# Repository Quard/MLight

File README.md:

# MLight

MLight is a compact, all-in-one control board designed to manage auxiliary tools for soldering equipment. It was primarily developed for an affordable Chinese digital microscope, aiming to reduce the number of power cords and to integrate lighting for the microscope. Additionally, it can control the fan of a basic DIY fume extractor, built using a PC fan and an aquarium coal filter, and provide power to a small external HDMI display for the microscope.

Features of the Control Board:

* Capable of being powered by an external DC 12V source or a QuickChange USB source.
* Bypasses power to the microscope only when the voltage is at 12V.
* Custom ring light with PWM (Pulse Width Modulation) brightness control.
* The PWM for the light is configurable at frequencies of 1 kHz, 4 kHz, 8 kHz, or 16 kHz to prevent image distortion from the microscope.
* Provides a 12V output for PC fan with PWM speed control support for the DIY fume extractor.
* Features a USB output of 1.5A for powering an external HDMI display.
* Includes an OLED display and encoder for easy control.
* Equipped with external EEPROM memory for storing and restoring settings.

[A brief demonstration video of the system in operation.](https://youtube.com/shorts/ih5DoEOJhLI)

## Controls

| Action | Description |
|--------|-------------|
| Encoder short press | Switch between fan and light |
| Encoder rotate | Change the value of current selected element |
| Encoder long press | Disable/enable fan and light |
| Encoder rotate pressed | Change the light PWM frequency |

## Project parts

### Firmware

The `firmware` folder includes an STM32CubeIDE CMake project, with all source code developed using CMSIS.

### Control Board

The KiCad project is located in the `hardware/control_board` directory. It includes a BOM file in the project root and an interactive BOM (iBOM) in the `bom` folder to facilitate assembly.

### Ring Light

The same structure applies to the Ring Light project, with its root located in the `hardware/ring_light` directory. It also contains a BOM file in the project root and an interactive BOM (iBOM) in the `bom` folder to assist with assembly.

### 3d

The `3d` folder contains STL files and Fusion 360 source files for the brackets used to mount the control board and ring light onto a microscope stand.

## Display elements

## Components block diagram

## BOM

### Control Board

|Reference|Value|Qty|Manufacturer Part Number|LCSC|MOUSER|
|---------|-----|---|------------------------|----|------|
|C1,C4,C10|100nF|3|CL10B104KB8NNNC|C1591|187-CL10B104KB8NNNC |
|C2|4.7uF|1|CL21A475KAQNNNE|C1779|187-CL21A475KAQNNNE |
|C3,C7,C8|10uF|3|CL21A106KOQNNNE|C1713|187-CL21A106KOQNNNE |
|C5,C6,C9|10nF|3|CL10B103JB8NNNC|C7248|187-CL10B103JB8NNNC |
|C11,C12|22uF|2|CL31A226KAHNNNE|C12891|187-CL31A226KAHNNNE |
|D1,D2|B340|2|B340A-13-F|C85098|621-B340A-F|
|D3|LED|1|150060BS75000|C84266|710-150060BS75000|
|D4|LED|1|150060RS75000|C84263|710-150060RS75000|
|IC1|FZT1049ATA|1|FZT1049ATA|C73835|522-FZT1049ATA|
|J1|USB_A_Stacked|1| 67298-4090|C908455|538-67298-4090|
|J3|Light|1||C158012||
|J4|Fan|1|47053-3000|C19795120|538-47053-3000|
|J5|OLED SSD1306|1||||
|J7|USB_C_Receptacle_USB2.0|1|GSB1C211110DS1HR|C709357|523-GSB1C211110DS1HR|
|J8|Barrel_Jack|1|KLDHCX-0202-BP-LT|C720558|806-KLDHCX0202BPLT|
|J9|Conn_01x02|1||C158012||
|L1|4.7uH|1|IHLP2525CZER4R7M01|C553961|70-IHLP2525CZER4R7M1|
|Q1|AO3400A|1|AO3400A|C20917|942-IRLML6344TRPBF|
|R1,R2,R3,R4,R5,R6,R8,R10,R15|10k|9|RC0603FR-0710KL|C98220|603-RC0603FR-0710KL|
|R7|180k|1|RC0603FR-07180KL|C123419|603-RC0603FR-07180KL|
|R9,R11|2.2k|2|RC0603FR-072K2L|C114662|603-RC0603FR-072K2L|
|R12|33k|1|RC0603FR-0733KL|C126359|603-RC0603FR-0733KL|
|R13,R16|1k|2|RC0603FR-071KL|C22548|603-RC0603FR-071KL|
|R14|1.8k|1|RC0603FR-071K8L|C185354|603-RC0603FR-071K8L|
|SW4|RotaryEncoder_Switch|1|C18164805|652-PEC12R-4220F-S24|PEC12R-4220F-S0024|
|U1|STM32G030F6Px|1|STM32G030F6P6TR|C529330|511-STM32G030F6P6TR|
|U2|AP63205WU|1|AP63205WU-7|C2071056|621-AP63205WU-7|
|U3|M24C02-WMN|1|M24C02-RMN6TP|C83836|511-M24C02-RMN6TP|
|U4|NCP1117-3.3_SOT223|1|NCP1117ST33T3G|C26537|863-NCP1117ST33T3G|

### Ring Light

|Reference|Value|Qty|Manufacturer Part Number|LCSC|MOUSER|
|---------|-----|---|------------------------|----|------|
|D1,D2,D3,D4,D5,D6,D7,D8,D9,D10,D11,D12,D13,D14,D15,D16|LED|16|JE2835AWT-R-H40EA0000-N0000001|C5220767|941-JE2835AWTH40EAN|
|R1,R2,R3,R4|0|4|RC0603JR-070RL|C95177|603-RC0603JR-070RL|

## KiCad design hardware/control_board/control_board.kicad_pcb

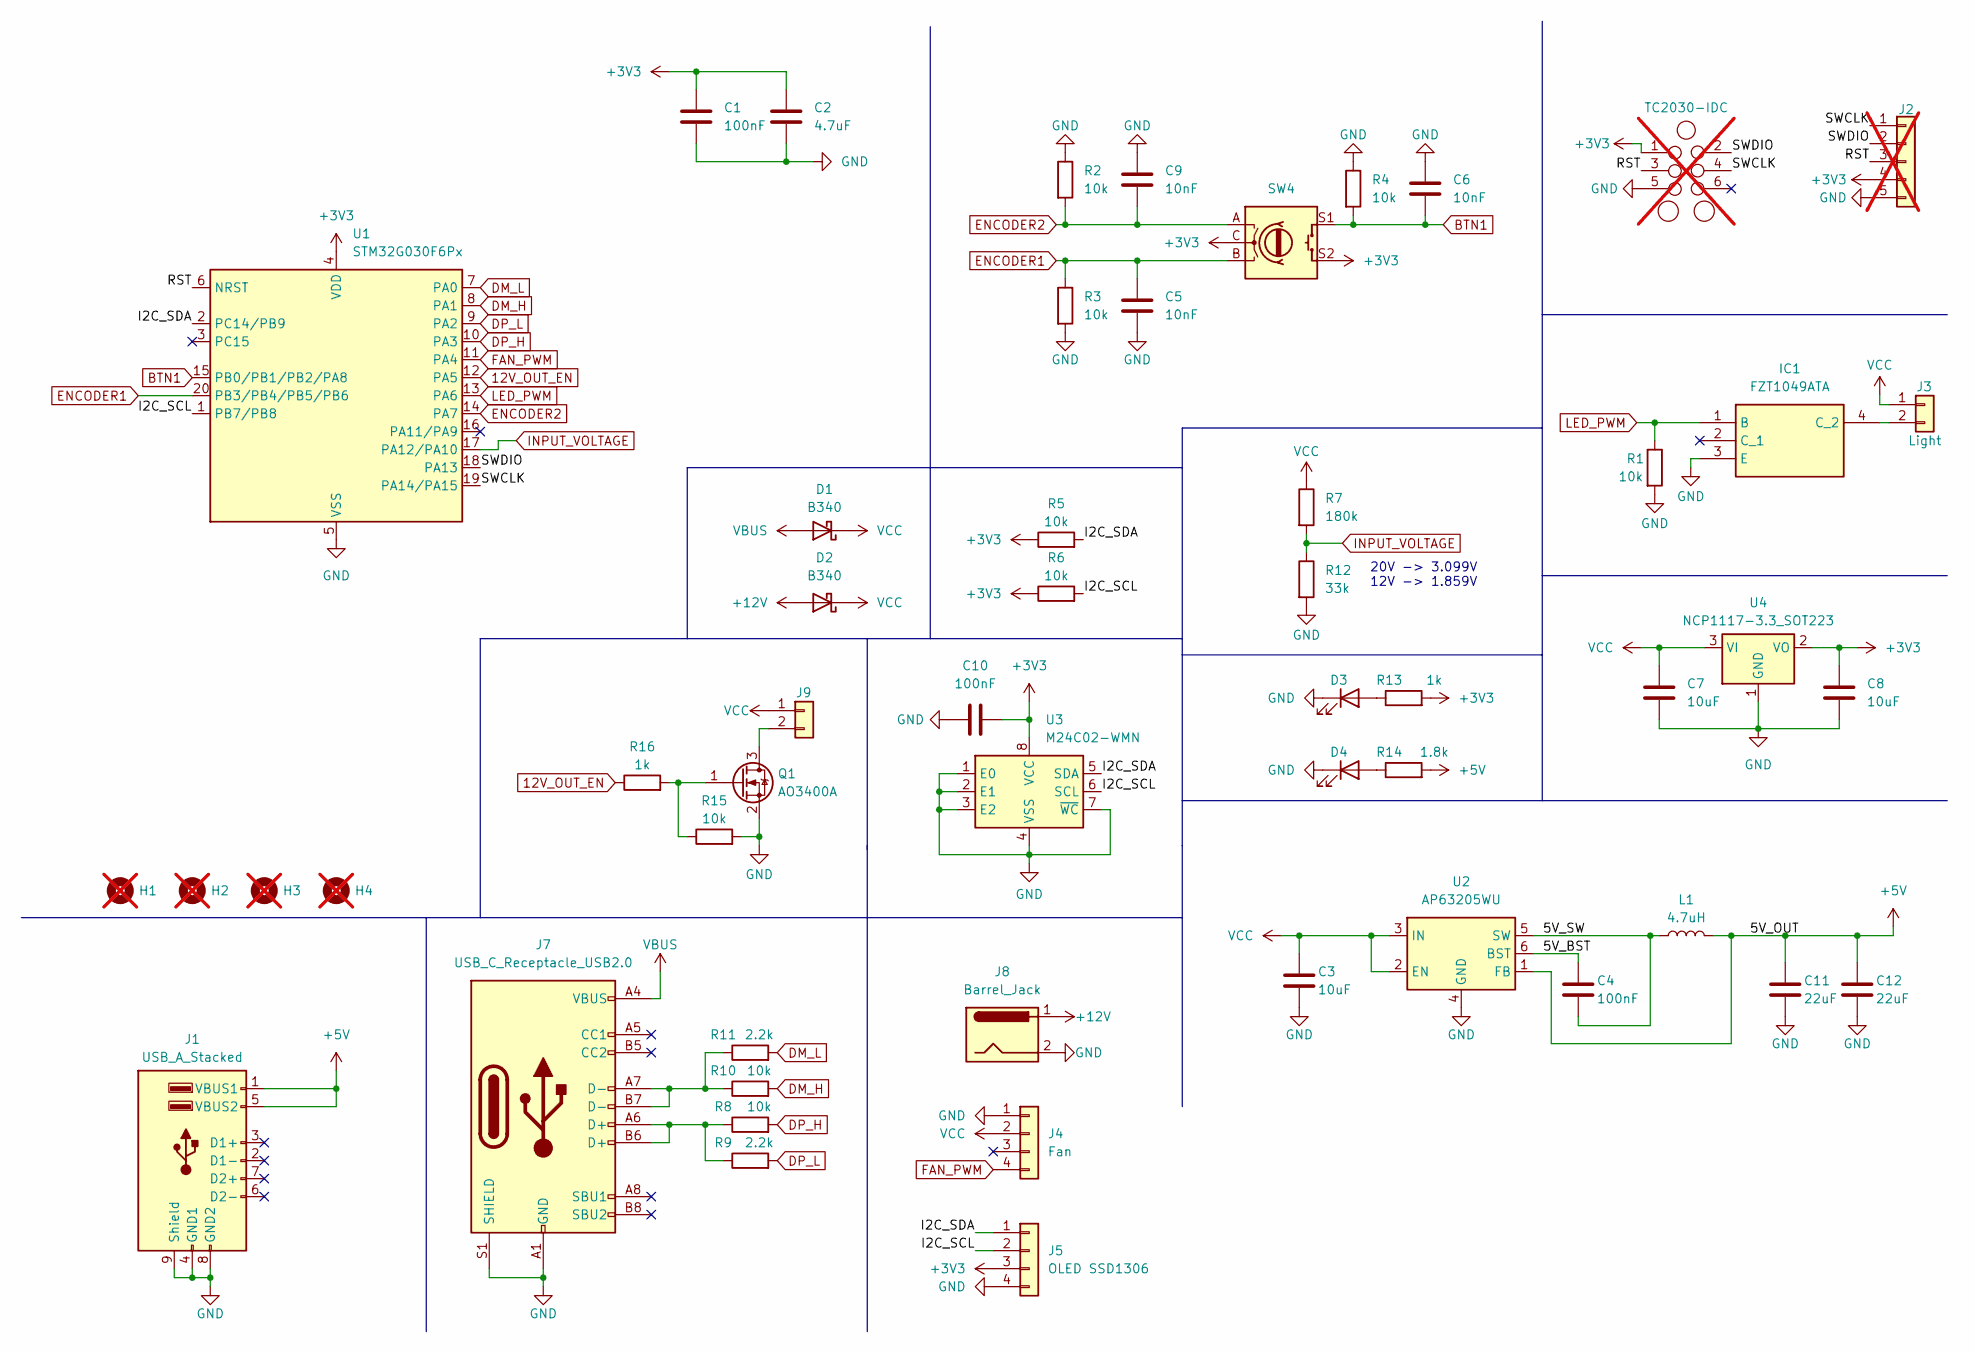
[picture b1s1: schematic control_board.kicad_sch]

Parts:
C1, C4, C10: 100nF; C_0603_1608Metric; Manufacturer_Part_Number CL10B104KB8NNNC; LCSC C1591
C2: 4.7uF; C_0805_2012Metric; Manufacturer_Part_Number CL21A475KAQNNNE; LCSC C1779
C3, C7, C8: 10uF; C_0805_2012Metric; Manufacturer_Part_Number CL21A106KOQNNNE; LCSC C1713
C5, C6, C9: 10nF; C_0603_1608Metric; Manufacturer_Part_Number CL10B103JB8NNNC; LCSC C7248
C11, C12: 22uF; C_1206_3216Metric; Manufacturer_Part_Number CL31A226KAHNNNE; LCSC C12891
D1, D2: B340; D_SMA; Manufacturer_Part_Number B340A-13-F; LCSC C85098
D3: LED; LED_0603_1608Metric; Manufacturer_Part_Number 150060BS75000; LCSC C84266
D4: LED; LED_0603_1608Metric; Manufacturer_Part_Number 150060RS75000; LCSC C84263
H1, H2, H3, H4: MountingHole; MountingHole_3.2mm_M3; not fitted
IC1: FZT1049ATA; SOT230P700X180-4N; Manufacturer_Part_Number FZT1049ATA; Mouser Part Number 522-FZT1049ATA
J1: USB_A_Stacked; USB_A_CUI_UJ2-ADH-TH_Horizontal_Stacked; Manufacturer_Part_Number 67298-4090; LCSC C908455
J2: Conn_01x05; PinHeader_1x05_P2.54mm_Vertical; not fitted
J3: Light; JST_XH_B2B-XH-A_1x02_P2.50mm_Vertical; LCSC C158012
J4: Fan; JST_XH_B4B-XH-A_1x04_P2.50mm_Vertical; Manufacturer_Part_Number 47053-3000; LCSC C19795120
J5: OLED SSD1306; JST_XH_B4B-XH-A_1x04_P2.50mm_Vertical
J6: TC2030-IDC; Tag-Connect_TC2030-IDC-NL_2x03_P1.27mm_Vertical; not fitted
J7: USB_C_Receptacle_USB2.0; USB_C_Receptacle_Palconn_UTC16-G; Manufacturer_Part_Number GSB1C211110DS1HR; LCSC C709357
J8: Barrel_Jack; BarrelJack_GCT_DCJ200-10-A_Horizontal; Manufacturer_Part_Number KLDHCX-0202-BP-LT; LCSC C720558
J9: Conn_01x02; JST_XH_B2B-XH-A_1x02_P2.50mm_Vertical; LCSC C158012
L1: 4.7uH; L_Vishay_IHLP-2525; Manufacturer_Part_Number IHLP2525CZER4R7M01; LCSC C553961
Q1: AO3400A; SOT-23; Manufacturer_Part_Number AO3400A; LCSC C20917
R1, R2, R3, R4, R5, R6, R8, R10, R15: 10k; R_0603_1608Metric; Manufacturer_Part_Number RC0603FR-0710KL; LCSC C98220
R7: 180k; R_0603_1608Metric; Manufacturer_Part_Number RC0603FR-07180KL; LCSC C123419
R9, R11: 2.2k; R_0603_1608Metric; Manufacturer_Part_Number RC0603FR-072K2L; LCSC C114662
R12: 33k; R_0603_1608Metric; Manufacturer_Part_Number RC0603FR-0733KL; LCSC C126359
R13, R16: 1k; R_0603_1608Metric; Manufacturer_Part_Number RC0603FR-071KL; LCSC C22548
R14: 1.8k; R_0603_1608Metric; Manufacturer_Part_Number RC0603FR-071K8L; LCSC C185354
SW4: RotaryEncoder_Switch; RotaryEncoder_Bourns_Vertical_PEC12R-3x17F-Sxxxx; Manufacturer_Part_Number 652-PEC12R-4220F-S24; LCSC C18164805
U1: STM32G030F6Px; TSSOP-20_4.4x6.5mm_P0.65mm; Manufacturer_Part_Number STM32G030F6P6TR; LCSC C529330
U2: AP63205WU; TSOT-23-6; Manufacturer_Part_Number AP63205WU-7; LCSC C2071056
U3: M24C02-WMN; SOIC-8_3.9x4.9mm_P1.27mm; Manufacturer_Part_Number M24C02-RMN6TP; LCSC C83836
U4: NCP1117-3.3_SOT223; SOT-223-3_TabPin2; Manufacturer_Part_Number NCP1117ST33T3G; LCSC C26537

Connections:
12V_OUT_EN: R16.1, U1.12 (PA5)
+3V3: C1.1, C2.1, C8.1, C10.2, J2.4, J5.3, J6.1, R5.1, R6.1, R13.2, SW4.C, SW4.S2, U1.4 (VDD), U3.8 (VCC), U4.2 (VO)
+5V: C11.1, C12.1, J1.1 (VBUS1), J1.5 (VBUS2), L1.2, R14.2, U2.1 (FB)
+12V: D2.2 (A), J8.1
/5V_BST: C4.1, U2.6 (BST)
/5V_SW: C4.2, L1.1, U2.5 (SW)
/I2C_SCL: J5.2, R6.2, U1.1 (PB7/PB8), U3.6 (SCL)
/I2C_SDA: J5.1, R5.2, U1.2 (PC14/PB9), U3.5 (SDA)
/RST: J2.3, J6.3, U1.6 (NRST)
/SWCLK: J2.1, J6.4, U1.19 (PA14/PA15)
/SWDIO: J2.2, J6.2, U1.18 (PA13)
BTN1: C6.2, R4.2, SW4.S1, U1.15 (PB0/PB1/PB2/PA8)
DM_H: R10.2, U1.8 (PA1)
DM_L: R11.2, U1.7 (PA0)
DP_H: R8.2, U1.10 (PA3)
DP_L: R9.2, U1.9 (PA2)
ENCODER1: C5.1, R3.1, SW4.B, U1.20 (PB3/PB4/PB5/PB6)
ENCODER2: C9.2, R2.2, SW4.A, U1.14 (PA7)
FAN_PWM: J4.4, U1.11 (PA4)
GND: C1.2, C2.2, C3.2, C5.2, C6.1, C7.2, C8.2, C9.1, C10.1, C11.2, C12.2, D3.1 (K), D4.1 (K), IC1.3 (E), J1.4 (GND1), J1.8 (GND2), J1.9 (Shield), J2.5, J4.1, J5.4, J6.5, J7.A1 (GND), J7.A12 (GND), J7.B1 (GND), J7.B12 (GND), J7.S1 (SHIELD), J8.2, Q1.2 (S), R1.2, R2.1, R3.2, R4.1, R12.2, R15.2, U1.5 (VSS), U2.4 (GND), U3.1 (E0), U3.2 (E1), U3.3 (E2), U3.4 (VSS), U3.7 (~WC), U4.1 (GND)
INPUT_VOLTAGE: R7.2, R12.1, U1.17 (PA12/PA10)
LED_PWM: IC1.1 (B), R1.1, U1.13 (PA6)
unnamed: D3.2 (A), R13.1
unnamed: D4.2 (A), R14.1
unnamed: IC1.4 (C_2), J3.2
unnamed: J7.A6 (D+), J7.B6 (D+), R8.1, R9.1
unnamed: J7.A7 (D-), J7.B7 (D-), R10.1, R11.1
unnamed: J9.2, Q1.3 (D)
unnamed: Q1.1 (G), R15.1, R16.2
VBUS: D1.2 (A), J7.A4 (VBUS), J7.A9 (VBUS), J7.B4 (VBUS), J7.B9 (VBUS)
VCC: C3.1, C7.1, D1.1 (K), D2.1 (K), J3.1, J4.2, J9.1, R7.1, U2.2 (EN), U2.3 (IN), U4.3 (VI)

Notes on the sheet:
20V -> 3.099V 12V -> 1.859V

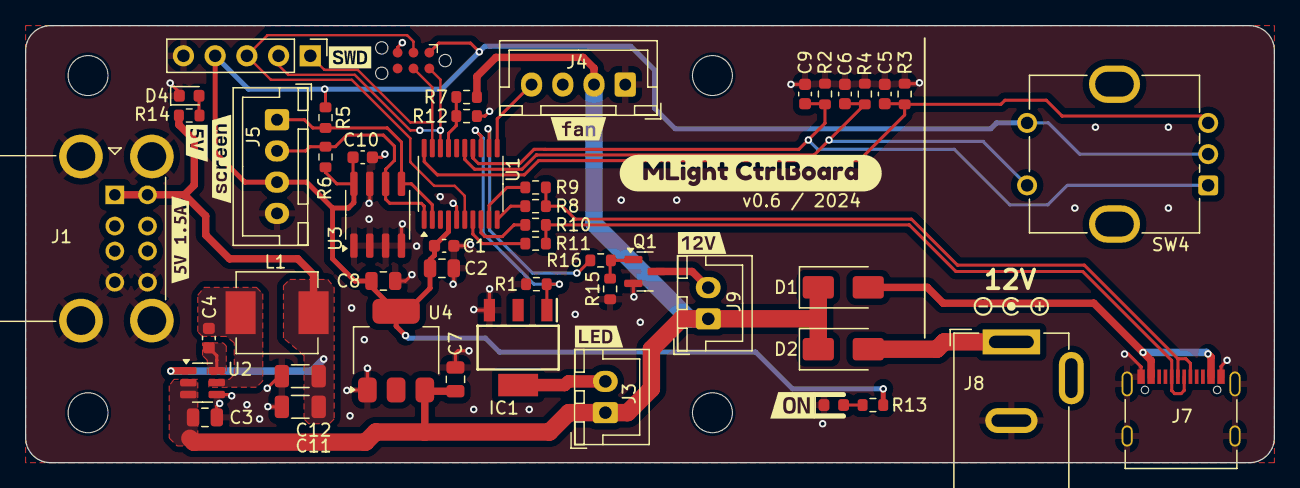
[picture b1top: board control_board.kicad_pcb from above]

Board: 2 copper layers, 100.0 x 35.0 mm, 62 parts (0 on the bottom side), 31 nets.

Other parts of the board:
kibuzzard-64DFCA22: G***; kibuzzard-64DFCA22
kibuzzard-64E1B8AF: G***; kibuzzard-64E1B8AF
kibuzzard-64E1B90C: G***; kibuzzard-64E1B90C
kibuzzard-64E666E4: G***; kibuzzard-64E666E4
kibuzzard-65854A39: G***; kibuzzard-65854A39
kibuzzard-6585330A: G***; kibuzzard-6585330A
kibuzzard-6585337F: G***; kibuzzard-6585337F
kibuzzard-65853391: G***; kibuzzard-65853391
kibuzzard-65855076: G***; kibuzzard-65855076

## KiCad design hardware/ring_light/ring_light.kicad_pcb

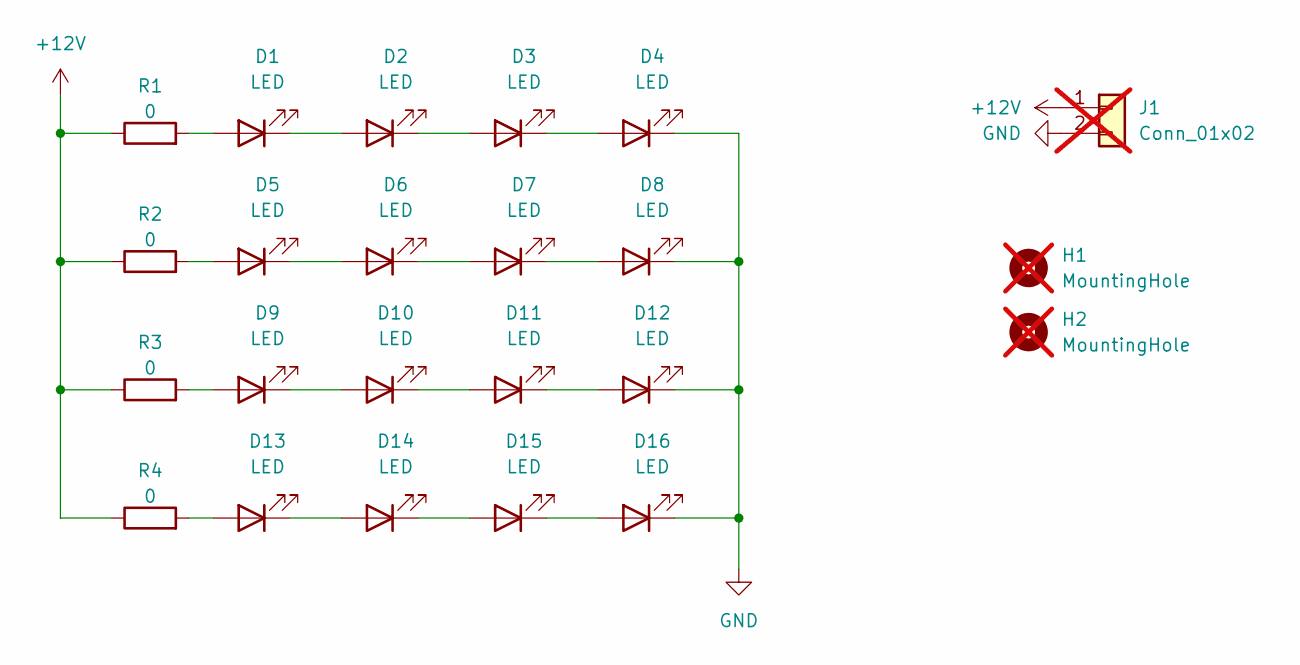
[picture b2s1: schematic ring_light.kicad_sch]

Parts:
D1, D2, D3, D4, D5, D6, D7, D8, D9, D10, D11, D12, D13, D14, D15, D16: LED; LED_PLCC_2835; Manufacturer Part Number JE2835AWT-R-H40EA0000-N0000001; LCSC C5220767
H1, H2: MountingHole; MountingHole_3.2mm_M3; not fitted
J1: Conn_01x02; PinHeader_1x02_P2.54mm_Vertical; not fitted
R1, R2, R3, R4: 0; R_0603_1608Metric; Manufacturer Part Number RC0603JR-070RL; LCSC C95177

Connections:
+12V: J1.1, R1.1, R2.1, R3.1, R4.1
GND: D4.1 (K), D8.1 (K), D12.1 (K), D16.1 (K), J1.2
unnamed: D1.2 (A), R1.2
unnamed: D1.1 (K), D2.2 (A)
unnamed: D2.1 (K), D3.2 (A)
unnamed: D3.1 (K), D4.2 (A)
unnamed: D5.2 (A), R2.2
unnamed: D5.1 (K), D6.2 (A)
unnamed: D6.1 (K), D7.2 (A)
unnamed: D7.1 (K), D8.2 (A)
unnamed: D9.2 (A), R3.2
unnamed: D9.1 (K), D10.2 (A)
unnamed: D10.1 (K), D11.2 (A)
unnamed: D11.1 (K), D12.2 (A)
unnamed: D13.2 (A), R4.2
unnamed: D13.1 (K), D14.2 (A)
unnamed: D14.1 (K), D15.2 (A)
unnamed: D15.1 (K), D16.2 (A)

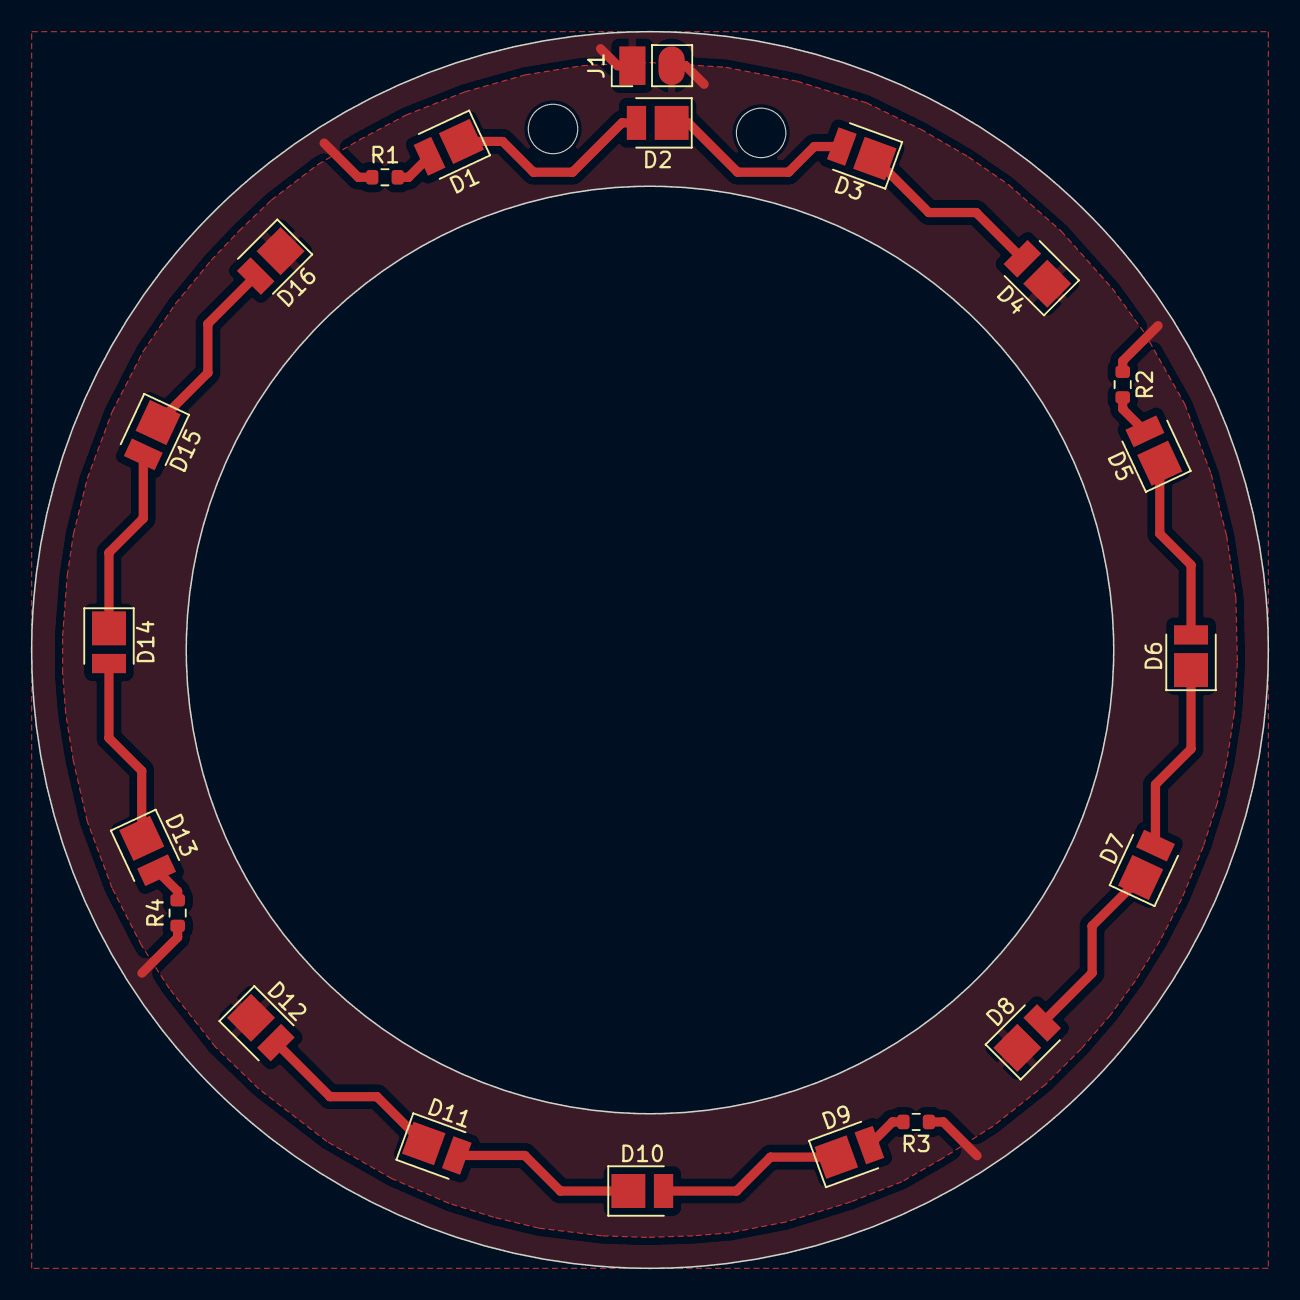
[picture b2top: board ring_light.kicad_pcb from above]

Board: 2 copper layers, 80.0 x 80.0 mm, 23 parts (0 on the bottom side), 18 nets.

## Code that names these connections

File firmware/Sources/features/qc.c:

#include "features/qc.h"


void _qc_dp_output(void);
void _qc_dm_output(void);
void _qc_dm_input(void);
void _qc_dp_set(qc_pin_mode_t mode);
void _qc_dm_set(qc_pin_mode_t mode);
uint8_t _qc_dm_is_high(void);


int8_t qc_init(qc_t *qc) {
	_qc_dp_output();
	_qc_dm_input();

	_qc_dp_set(QC_PIN_33);
	delay_ms(QC_DELAY_START_CHECK);
	if (_qc_dm_is_high()) {
		qc->mode = QC_MODE_5V;
		qc->voltage = 50;
	} else {
		return QC_RET_NOT_SUPPORTED;
	}

	_qc_dp_set(QC_PIN_06);
	delay_ms(QC_DELAY_HANDSHAKE);

	_qc_dp_set(QC_PIN_33);
	delay_ms(QC_DELAY_START_CHECK);
	if (_qc_dm_is_high()) {
		return QC_RET_10_ONLY;
	}

	_qc_dm_output();

	return QC_RET_OK;
}

void qc_set_mode(qc_t *qc, qc_mode_t mode) {
	if (qc->mode == QC_MODE_CONTINUOUS && mode != QC_MODE_CONTINUOUS) {
		// transition from the Continuous Mode to any other mode requires to switch to 5V mode first
		_qc_dp_set(QC_PIN_06);
		_qc_dm_set(QC_PIN_GND);
		delay_ms(QC_DELAY_NEW_MODE);

		if (mode == QC_MODE_5V) {
			qc->mode = QC_MODE_5V;
			qc->voltage = 50;
			return;
		}
	}

	switch (mode) {
	case QC_MODE_5V:
		_qc_dp_set(QC_PIN_06);
		_qc_dm_set(QC_PIN_GND);
		qc->voltage = 50;
		break;
	case QC_MODE_9V:
		_qc_dp_set(QC_PIN_33);
		_qc_dm_set(QC_PIN_06);
		qc->voltage = 90;
		break;
	case QC_MODE_12V:
		_qc_dp_set(QC_PIN_06);
		_qc_dm_set(QC_PIN_06);
		qc->voltage = 120;
		break;
	case QC_MODE_20V:
		_qc_dp_set(QC_PIN_33);
		_qc_dm_set(QC_PIN_33);
		qc->voltage = 200;
		break;
	case QC_MODE_CONTINUOUS:
		_qc_dp_set(QC_PIN_06);
		_qc_dm_set(QC_PIN_33);
		break;
	}

	qc->mode = mode;
	delay_ms(QC_DELAY_NEW_MODE);
}

void _qc_dp_output(void) {
	// PA2 + PA3
	GPIOA->MODER &= ~(0b1111 << 4);
	GPIOA->MODER |= (0b0101 << 4);
}

void _qc_dm_output(void) {
	// PA0 + PA1
	GPIOA->MODER &= ~(0b1111 << 0);
	GPIOA->MODER |= (0b0101 << 0);
}

void _qc_dm_input(void) {
	// PA0 + PA1
	GPIOA->MODER &= ~(0b1111 << 0);
}

void _qc_dp_set(qc_pin_mode_t mode) {
	switch (mode) {
	case QC_PIN_GND:
		GPIOA->ODR &= ~(0b11 << 2);
		break;
	case QC_PIN_06:
		GPIOA->ODR &= ~(0b11 << 2);
		GPIOA->ODR |= (0b1 << 3);
		break;
	case QC_PIN_33:
		GPIOA->ODR |= (0b11 << 2);
		break;
	}
}

void _qc_dm_set(qc_pin_mode_t mode) {
	switch (mode) {
	case QC_PIN_GND:
		GPIOA->ODR &= ~(0b11 << 0);
		break;
	case QC_PIN_06:
		GPIOA->ODR &= ~(0b11 << 0);
		GPIOA->ODR |= (0b1 << 1);
		break;
	case QC_PIN_33:
		GPIOA->ODR |= (0b11 << 0);
		break;
	}
}

uint8_t _qc_dm_is_high(void) {
	return GPIOA->IDR & 0b11 ? 1 : 0;
}

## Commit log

2024-10-09 publishing the project
